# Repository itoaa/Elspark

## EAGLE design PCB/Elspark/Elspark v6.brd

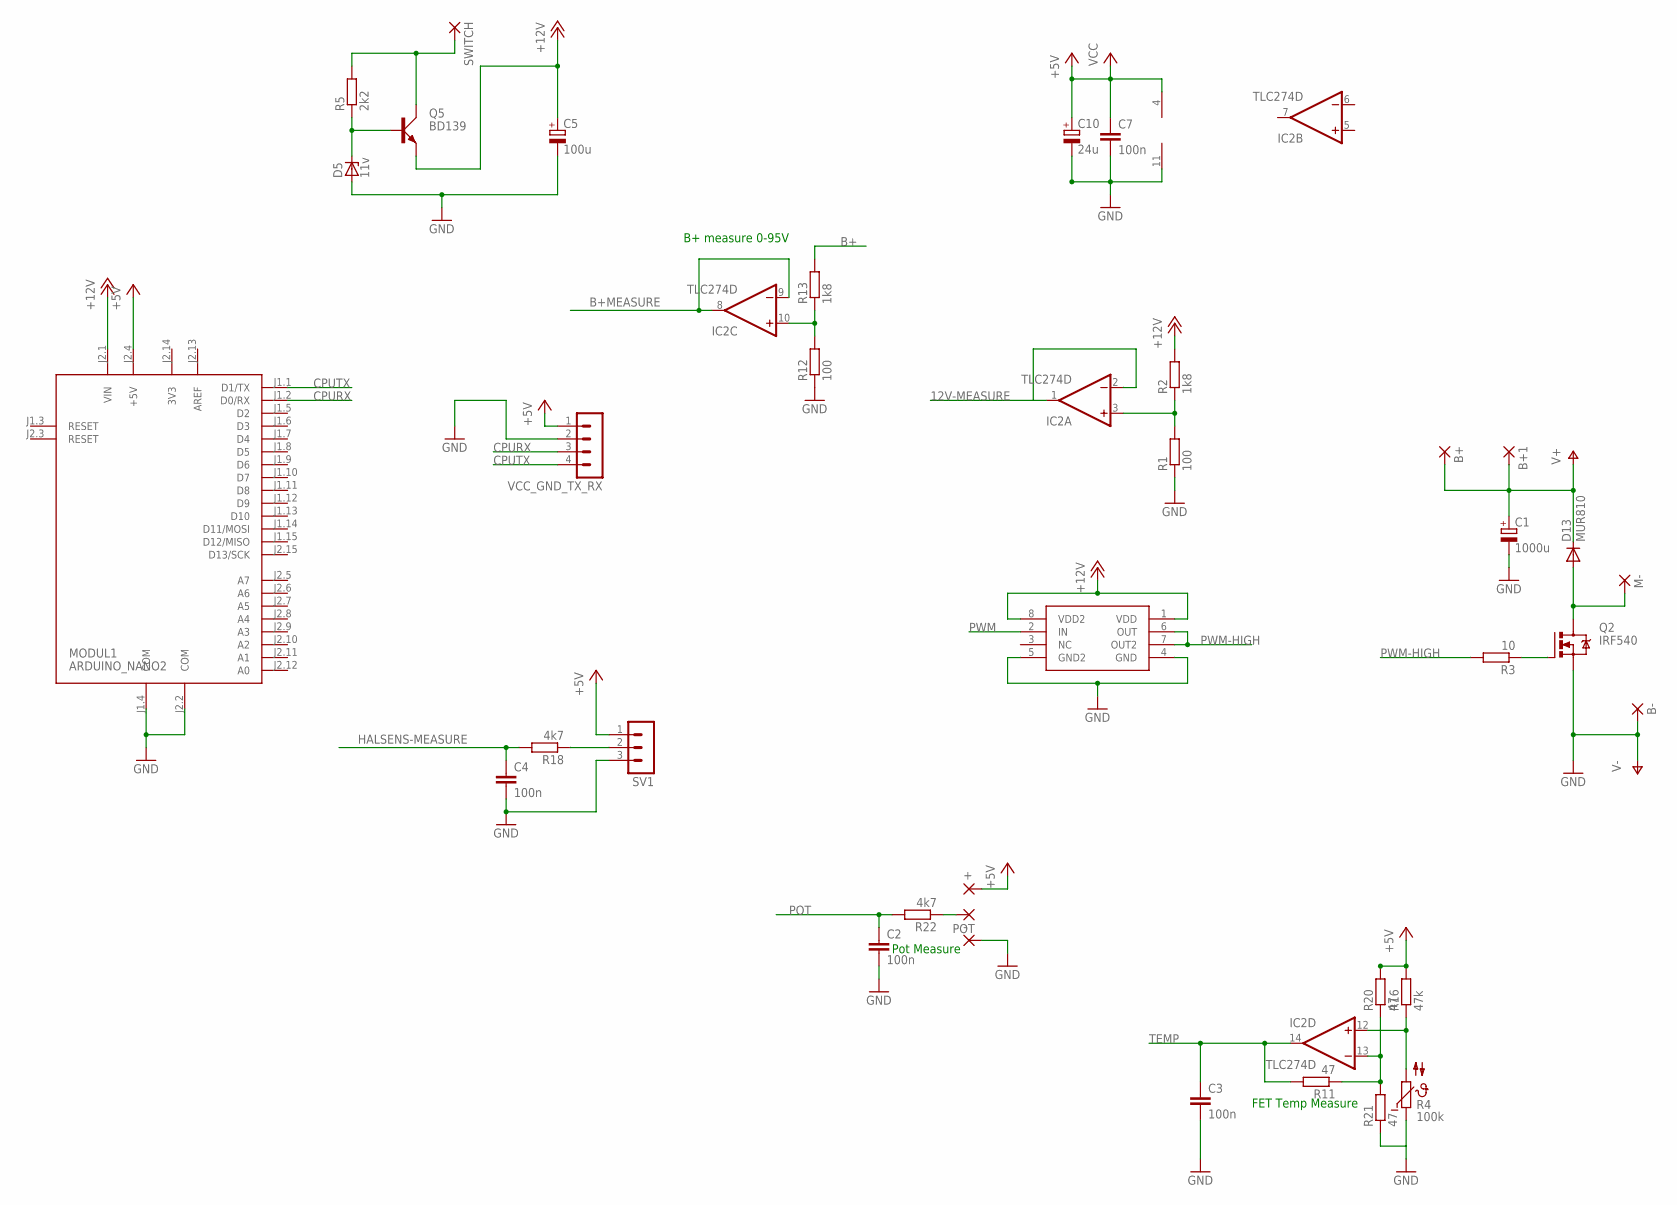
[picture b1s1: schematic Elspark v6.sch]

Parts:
+: 2,15/1,0
-: 2,15/1,0
B+, B+1: WIREPAD4,16O1,6; 4,16O1,6
B-: WIREPAD4,16O1,6; 4,16O1,6
C1: 1000u; E7,5-16
C2, C3, C4, C7: 100n; C050-024X044
C5: 100u; E2,5-5
C10: 24u; E2,5-5
D5: 11v; DO35Z10
D13: MUR810; TO220ACS
IC2: TLC274D; SO14
M-: WIREPAD4,16O1,6; 4,16O1,6
MODUL1: ARDUINO_NANO2
POT: 2,15/1,0
Q2: IRF540; TO220BV
Q5: BD139; TO126AV
R1, R12: 100; 0204/7
R2, R13: 1k8; 0204/7
R3: 10; 0207/2V
R4: 100k; N640
R5: 2k2; 0207/2V
R11, R20, R21: 47; 0207/2V
R16: 47k; 0207/2V
R18: 4k7; 0204/7
R22: 4k7; 0207/2V
SV1: MA03-1
SWITCH: 1,6/0,9
U$1: MIC4451SO-8; SO-8
VCC_GND_TX_RX: MA04-1

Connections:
3V3: MODUL1.J2.14 (3V3)
12V-MEASURE: IC2.1 (OUT), IC2.2 (-IN)
+5V: MODUL1.J2.4 (+5V), R16.2, R20.2, SV1.1, VCC_GND_TX_RX.1
+12V: C5.+, MODUL1.J2.1 (VIN), Q5.E, R2.2, U$1.1 (VDD), U$1.8 (VDD2)
AREF: MODUL1.J2.13 (AREF)
B+: B+.1, B+1.1, C1.+, D13.C, R13.2
B+MEASURE: IC2.8 (OUT), IC2.9 (-IN)
CPURX: MODUL1.J1.2 (D0/RX), VCC_GND_TX_RX.3
CPUTX: MODUL1.J1.1 (D1/TX), VCC_GND_TX_RX.4
GND: -.1, B-.1, C1.-, C2.2, C3.2, C4.2, C5.-, C7.2, C10.-, D5.A, IC2.11 (V-), MODUL1.J1.4 (COM), MODUL1.J2.2 (COM), Q2.S, R1.1, R4.1, R12.1, R21.1, SV1.3, U$1.4 (GND), U$1.5 (GND2), VCC_GND_TX_RX.2
HALSENS-MEASURE: C4.1, R18.2
M+: D13.A, M-.1, Q2.D
unnamed: IC2.3 (+IN), R1.2, R2.1
unnamed: Q2.G, R3.1
unnamed: IC2.10 (+IN), R12.2, R13.1
unnamed: D5.C, Q5.B, R5.1
unnamed: R18.1, SV1.2
unnamed: IC2.13 (-IN), R11.1, R20.1, R21.2
unnamed: POT.1, R22.1
unnamed: IC2.12 (+IN), R4.2, R16.1
unnamed: Q5.C, R5.2, SWITCH.1
POT: C2.1, R22.2
PWM: U$1.2 (IN)
PWM-HIGH: R3.2, U$1.6 (OUT), U$1.7 (OUT2)
TEMP: C3.1, IC2.14 (OUT), R11.2
VCC: +.1, C7.1, C10.+, IC2.4 (V+)

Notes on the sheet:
B+ measure 0-95V
Pot Measure
FET Temp Measure

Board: 2 copper layers, 37 parts (0 on the bottom side), 23 nets, no tracks yet.

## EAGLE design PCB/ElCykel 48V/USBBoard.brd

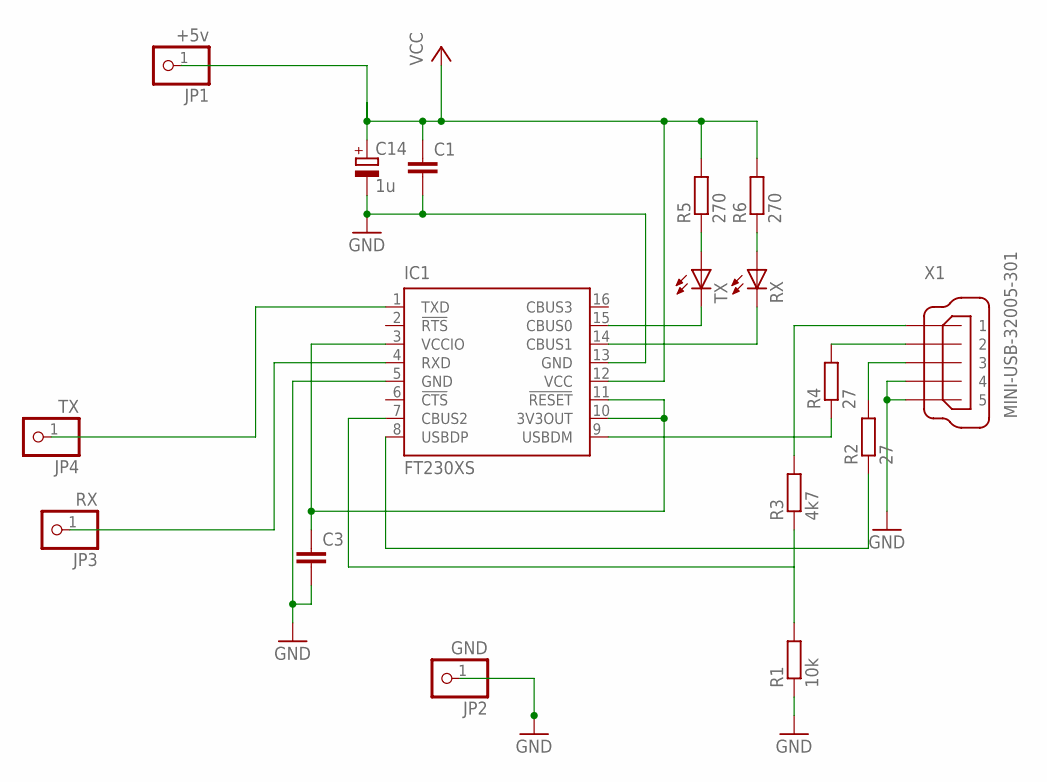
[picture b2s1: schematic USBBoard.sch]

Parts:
C1, C3: C-EU050-025X075; C050-025X075
C14: 1u; E2-4
IC1: FT230XS; SSOP16
JP1: +5v; 1X01
JP2: GND; 1X01
JP3: RX; 1X01
JP4: TX; 1X01
R1: 10k; 0207/2V
R2, R4: 27; 0207/2V
R3: 4k7; 0207/2V
R5, R6: 270; 0207/2V
RX: LED3MM
TX: LED3MM
X1: MINI-USB-32005-301; 32005-301

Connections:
GND: C1.2, C3.2, C14.-, IC1.5 (GND), IC1.13 (GND), JP2.1, R1.1, X1.4, X1.5
unnamed: IC1.1 (TXD), JP4.1
unnamed: IC1.4 (RXD), JP3.1
unnamed: C3.1, IC1.3 (VCCIO), IC1.10 (3V3OUT), IC1.11 (!RESET)
unnamed: R3.2, X1.1
unnamed: R2.2, X1.3
unnamed: R4.2, X1.2
unnamed: IC1.7 (CBUS2), R1.2, R3.1
unnamed: IC1.9 (USBDM), R4.1
unnamed: IC1.8 (USBDP), R2.1
unnamed: IC1.14 (CBUS1), RX.K (C)
unnamed: IC1.15 (CBUS0), TX.K (C)
unnamed: R5.1, TX.A
unnamed: R6.1, RX.A
VCC: C1.1, C14.+, IC1.12 (VCC), JP1.1, R5.2, R6.2

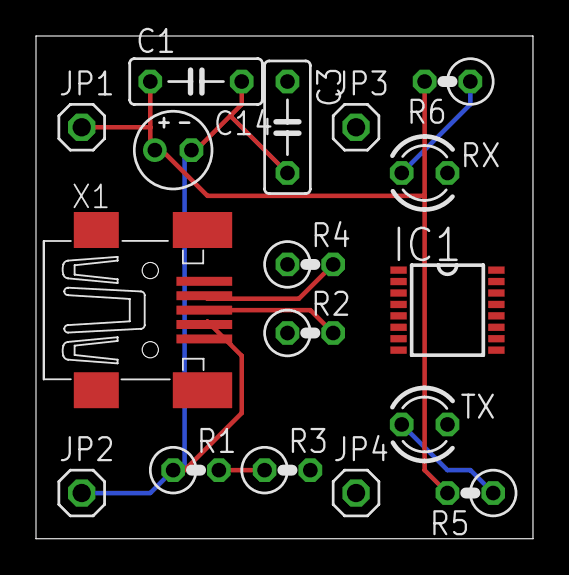
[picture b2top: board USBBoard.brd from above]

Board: 2 copper layers, 27.6 x 27.9 mm, 17 parts (0 on the bottom side), 15 nets.

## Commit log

2014-05-14 Move from SDN
2014-05-19 PCR redesign
2014-05-20 New Elspark v6 arduino board
2014-06-09 New PCB
